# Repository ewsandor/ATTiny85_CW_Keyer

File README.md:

# ATTiny85_CW_Keyer
A full-featured CW keyer for amateur radio use. The keyer is built around a cheap and tiny ATTINY85 microcontroller. The circuit boasts 4-100 character memories, beacon mode, multiple timing options, and a CW trainer for improving your Morse code speed.

## Printed Circuit Board
This fork provides design files to build a PCB for this project.

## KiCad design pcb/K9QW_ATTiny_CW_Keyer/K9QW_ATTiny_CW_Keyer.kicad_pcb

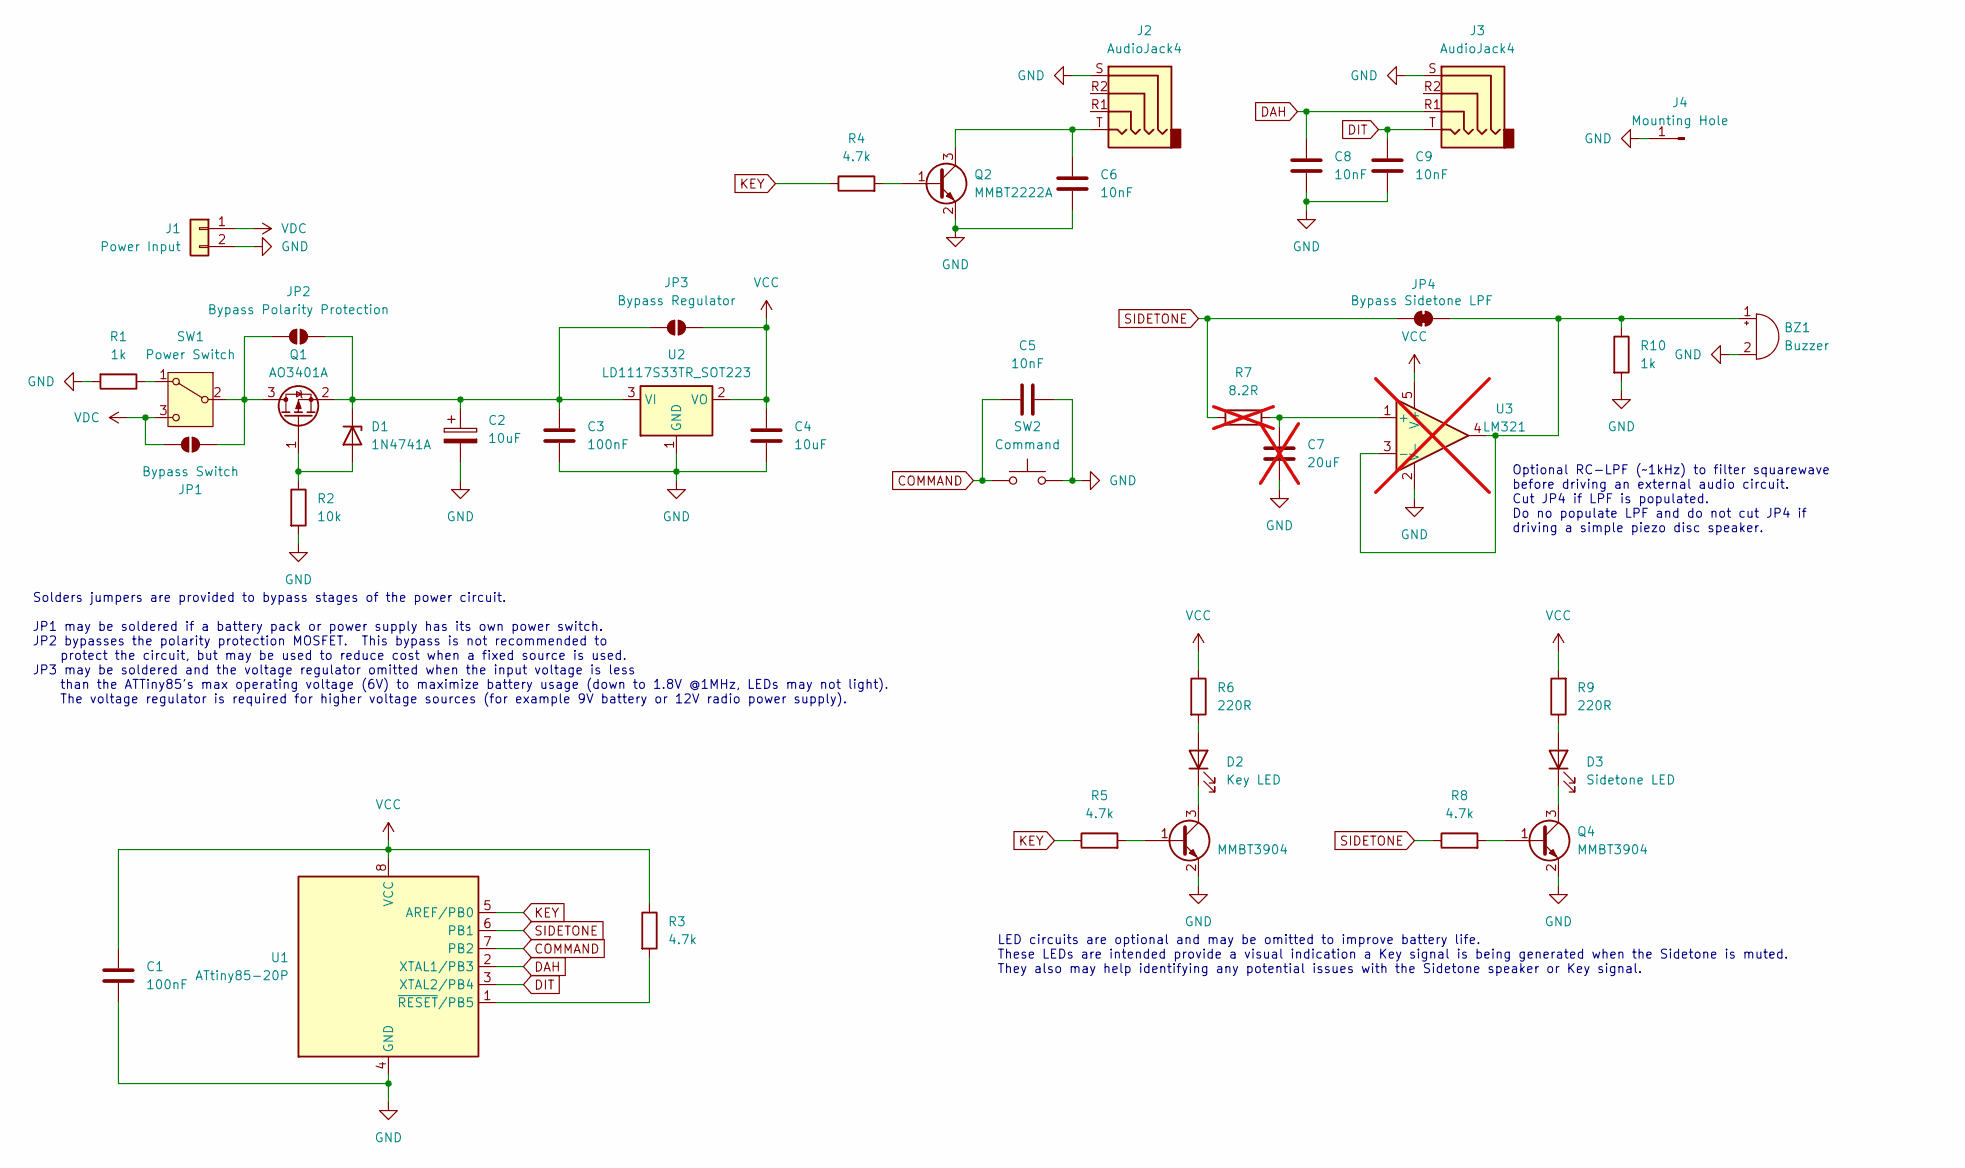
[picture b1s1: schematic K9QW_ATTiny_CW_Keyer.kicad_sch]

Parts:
BZ1: Buzzer; Buzzer_TDK_PS1240P02BT_D12.2mm_H6.5mm
C1, C3: 100nF; C_0603_1608Metric_Pad1.08x0.95mm_HandSolder
C2: 10uF; CP_Radial_D5.0mm_P2.00mm
C4: 10uF; C_0603_1608Metric_Pad1.08x0.95mm_HandSolder
C5, C6, C8, C9: 10nF; C_0603_1608Metric_Pad1.08x0.95mm_HandSolder
C7: 20uF; C_0603_1608Metric_Pad1.08x0.95mm_HandSolder; not fitted
D1: 1N4741A; D_DO-41_SOD81_P3.81mm_Vertical_KathodeUp
D2: Key LED; LED_0603_1608Metric_Pad1.05x0.95mm_HandSolder
D3: Sidetone LED; LED_0603_1608Metric_Pad1.05x0.95mm_HandSolder
J1: Power Input; JST_XH_B2B-XH-A_1x02_P2.50mm_Vertical
J2, J3: AudioJack4; Jack_3.5mm_PJ320D_Horizontal
J4: Mounting Hole; MountingHole_3.2mm_M3_Pad_TopBottom
JP1: Bypass Switch; SolderJumper-2_P1.3mm_Open_RoundedPad1.0x1.5mm
JP2: Bypass Polarity Protection; SolderJumper-2_P1.3mm_Open_RoundedPad1.0x1.5mm
JP3: Bypass Regulator; SolderJumper-2_P1.3mm_Open_RoundedPad1.0x1.5mm
JP4: Bypass Sidetone LPF; SolderJumper-2_P1.3mm_Bridged_RoundedPad1.0x1.5mm
Q1: AO3401A; SOT-23
Q2: MMBT2222A; SOT-23
Q3, Q4: MMBT3904; SOT-23
R1, R10: 1k; R_0603_1608Metric_Pad0.98x0.95mm_HandSolder
R2: 10k; R_0603_1608Metric_Pad0.98x0.95mm_HandSolder
R3, R4, R5, R8: 4.7k; R_0603_1608Metric_Pad0.98x0.95mm_HandSolder
R6, R9: 220R; R_0603_1608Metric_Pad0.98x0.95mm_HandSolder
R7: 8.2R; R_0603_1608Metric_Pad0.98x0.95mm_HandSolder; not fitted
SW1: Power Switch; JST_XH_B3B-XH-A_1x03_P2.50mm_Vertical
SW2: Command; SW_PUSH_6mm
U1: ATtiny85-20P; DIP-8_W7.62mm
U2: LD1117S33TR_SOT223; SOT-223-3_TabPin2
U3: LM321; SOT-23-5; not fitted

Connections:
COMMAND: C5.1, SW2.1, U1.7 (PB2)
DAH: C8.1, J3.R1, U1.2 (XTAL1/PB3)
DIT: C9.1, J3.T, U1.3 (XTAL2/PB4)
GND: BZ1.2 (-), C1.2, C2.2, C3.2, C4.2, C5.2, C6.2, C7.2, C8.2, C9.2, J1.2, J2.S, J3.S, J4.1, Q2.2 (E), Q3.2 (E), Q4.2 (E), R1.2, R2.2, R10.2, SW2.2, U1.4 (GND), U2.1 (GND), U3.2 (V-)
KEY: R4.1, R5.1, U1.5 (AREF/PB0)
unnamed: BZ1.1 (+), JP4.2 (B), R10.1, U3.3 (-), U3.4
unnamed: D1.2 (A), Q1.1 (G), R2.1
unnamed: C2.1, C3.1, D1.1 (K), JP2.2 (B), JP3.1 (A), Q1.2 (S), U2.3 (VI)
unnamed: D2.2 (A), R6.2
unnamed: D2.1 (K), Q3.3 (C)
unnamed: D3.2 (A), R9.1
unnamed: D3.1 (K), Q4.3 (C)
unnamed: JP1.1 (A), JP2.1 (A), Q1.3 (D), SW1.2 (B)
unnamed: Q2.1 (B), R4.2
unnamed: C6.1, J2.T, Q2.3 (C)
unnamed: Q3.1 (B), R5.2
unnamed: Q4.1 (B), R8.2
unnamed: R1.1, SW1.1 (A)
unnamed: R3.2, U1.1 (~RESET/PB5)
unnamed: C7.1, R7.1, U3.1 (+)
SIDETONE: JP4.1 (A), R7.2, R8.1, U1.6 (PB1)
VCC: C1.1, C4.1, JP3.2 (B), R3.1, R6.1, R9.2, U1.8 (VCC), U2.2 (VO), U3.5 (V+)
VDC: J1.1, JP1.2 (B), SW1.3 (C)

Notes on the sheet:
Optional RC-LPF (~1kHz) to filter squarewave before driving an external audio circuit. Cut JP4 if LPF is populated. Do no populate LPF and do not cut JP4 if driving a simple piezo disc speaker.
LED circuits are optional and may be omitted to improve battery life. These LEDs are intended provide a visual indication a Key signal is being generated when the Sidetone is muted. They also may help identifying any potential issues with the Sidetone speaker or Key signal.
Solders jumpers are provided to bypass stages of the power circuit. JP1 may be soldered if a battery pack or power supply has its own power switch. JP2 bypasses the polarity protection MOSFET. This bypass is not recommended to protect the circuit, but may be used to reduce cost when a fixed source 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

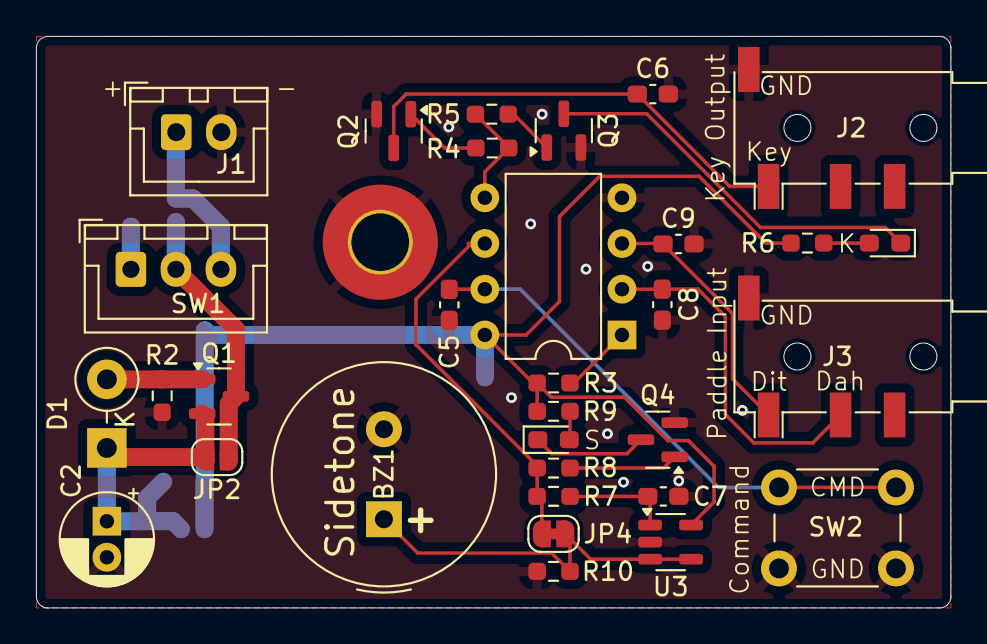
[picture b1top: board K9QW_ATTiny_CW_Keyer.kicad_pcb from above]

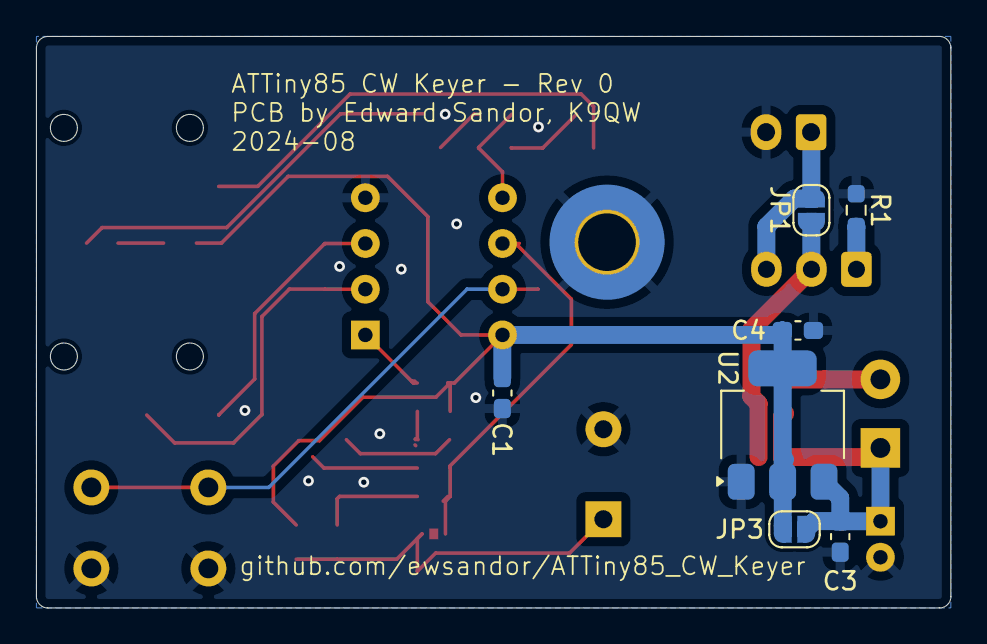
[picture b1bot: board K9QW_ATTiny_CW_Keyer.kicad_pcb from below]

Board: 2 copper layers, 50.8 x 31.8 mm, 40 parts (7 on the bottom side), 23 nets.

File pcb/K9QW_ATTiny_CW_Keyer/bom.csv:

"Reference","Value","Footprint","Qty","DNP"
"BZ1","Buzzer","Buzzer_Beeper:Buzzer_TDK_PS1240P02BT_D12.2mm_H6.5mm","1",""
"C1,C3","100nF","Capacitor_SMD:C_0603_1608Metric_Pad1.08x0.95mm_HandSolder","2",""
"C2","10uF","Capacitor_THT:CP_Radial_D5.0mm_P2.00mm","1",""
"C4","10uF","Capacitor_SMD:C_0603_1608Metric_Pad1.08x0.95mm_HandSolder","1",""
"C5,C6,C8,C9","10nF","Capacitor_SMD:C_0603_1608Metric_Pad1.08x0.95mm_HandSolder","4",""
"C7","20uF","Capacitor_SMD:C_0603_1608Metric_Pad1.08x0.95mm_HandSolder","1","DNP"
"D1","1N4741A","Diode_THT:D_DO-41_SOD81_P3.81mm_Vertical_KathodeUp","1",""
"D2","Key LED","LED_SMD:LED_0603_1608Metric_Pad1.05x0.95mm_HandSolder","1",""
"D3","Sidetone LED","LED_SMD:LED_0603_1608Metric_Pad1.05x0.95mm_HandSolder","1",""
"J1","Power Input","Connector_JST:JST_XH_B2B-XH-A_1x02_P2.50mm_Vertical","1",""
"J2,J3","AudioJack4","Connector_Audio:Jack_3.5mm_PJ320D_Horizontal","2",""
"J4","Mounting Hole","MountingHole:MountingHole_3.2mm_M3_Pad_TopBottom","1",""
"Q1","AO3401A","Package_TO_SOT_SMD:SOT-23","1",""
"Q2","MMBT2222A","Package_TO_SOT_SMD:SOT-23","1",""
"Q3,Q4","MMBT3904","Package_TO_SOT_SMD:SOT-23","2",""
"R1","1k","Resistor_SMD:R_0603_1608Metric_Pad0.98x0.95mm_HandSolder","1",""
"R2","10k","Resistor_SMD:R_0603_1608Metric_Pad0.98x0.95mm_HandSolder","1",""
"R3,R4,R5,R8","4.7k","Resistor_SMD:R_0603_1608Metric_Pad0.98x0.95mm_HandSolder","4",""
"R6,R9","220R","Resistor_SMD:R_0603_1608Metric_Pad0.98x0.95mm_HandSolder","2",""
"R7","8.2R","Resistor_SMD:R_0603_1608Metric_Pad0.98x0.95mm_HandSolder","1","DNP"
"SW1","Power Switch","Connector_JST:JST_XH_B3B-XH-A_1x03_P2.50mm_Vertical","1",""
"SW2","Command","Button_Switch_THT:SW_PUSH_6mm","1",""
"U1","ATtiny85-20P","Package_DIP:DIP-8_W7.62mm","1",""
"U2","LD1117S33TR_SOT223","Package_TO_SOT_SMD:SOT-223-3_TabPin2","1",""
"U3","LM321","Package_TO_SOT_SMD:SOT-23-5","1","DNP"

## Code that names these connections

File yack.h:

/* ********************************************************************
 Program	: yack.h
 Author		: Jan Lategahn DK3LJ modified by Jack Welch AI4SV, Don Froula WD9DMP
 Purpose	: definition of keyer hardware
 Created	: 15.10.2010
 Update		: 23.12.2016
 Version	: 0.86
 
 Changelog
 ---------
 Version		Date		Change
 ----------------------------------------------------------------------
0.86          23.12.2016    Changed sidetone back to 800 Hz and mode default to iambicB  
 
 Todo
 ----
 
 
 *********************************************************************/

// User configurable settings

// The following settings define the hardware connections to the keyer chip

// Definition of where the keyer itself is connected 
#define		KEYDDR			DDRB
#define		KEYPORT			PORTB
#define		KEYINP			PINB
#define		DITPIN			4
#define		DAHPIN			3

// Definition of where the transceiver keyer line is connected
#define		OUTDDR			DDRB
#define		OUTPORT			PORTB
#define		OUTPIN			0

// Definition of where the sidetone output is connected (beware,
// this is chip dependent and can not just be changed at will)
#define		STDDR			DDRB
#define		STPORT			PORTB
#define		STPIN			1

// Definition of where the control button is connected
#define		BTNDDR			DDRB
#define		BTNPORT			PORTB
#define		BTNINP			PINB
#define		BTNPIN			2


// The following defines the meaning of status bits in the yackflags and volflags 
// global variables

// Definition of the yackflags variable. These settings get stored in EEPROM when changed.
#define		NOTUSED1		0b00000001  // Available
#define     CONFLOCK		0b00000010  // Configuration locked down
#define		MODE			0b00001100  // 2 bits to define keyer mode (see next section)
#define		SIDETONE		0b00010000  // Set if the chip must produce a sidetone
#define		TXKEY			0b00100000  // Set if the chip keys the transmitter
#define		TXINV			0b01000000  // Set if TX key line is active low
#define		PDLSWAP			0b10000000  // Set if DIT and DAH are swapped

#define		IAMBICA			0b00000000  // IAMBIC A mode
#define		IAMBICB			0b00000100  // IAMBIC B mode (default)
#define		ULTIMATIC		0b00001000  // Ultimatic Mode
#define		DAHPRIO			0b00001100  // Always give DAH priority

#define		FLAGDEFAULT		IAMBICB | TXKEY | SIDETONE

// Definition of volflags variable. These flags do not get stored in EEPROM.
#define		DITLATCH		0b00000001  // Set if DIT contact was closed
#define     DAHLATCH		0b00000010  // Set if DAH contact was closed
#define     SQUEEZED        0b00000011  // DIT and DAH = squeezed
#define		DIRTYFLAG		0b00000100  // Set if cfg data was changed and needs storing
#define     CKLATCH         0b00001000  // Set if the command key was pressed at some point
#define		VSCOPY          0b00110000  // Copies of Sidetone and TX flags from yackflags


// The following defines timing constants. In the default version the keyer is set to operate in
// 10ms heartbeat intervals. If a higher resolution is required, this can be changed to a faster
// beat

// YACK heartbeat frequency (in ms)
#define		YACKBEAT		5
#define		YACKSECS(n)		(n*(1000/YACKBEAT)) // Beats in n seconds (off by 2x for 5ms heartbeat)
#define		YACKMS(n)		(n/YACKBEAT) // Beats in n milliseconds

// Power save mode
#define     POWERSAVE       // Comment this line if no power save mode required
#define     PSTIME          20 // 20 seconds until automatic powerdown
#define     PWRWAKE         ((1<<PCINT3) | (1<<PCINT4) | (1<<PCINT2)) // Dit, Dah or Command wakes us up..

// These values limit the speed that the keyer can be set to
#define		MAXWPM			50  
#define		MINWPM			5
#define		DEFWPM			15

// Farnsworth parameters
#define     FARNSWORTH      1
#define     WPMSPEED        0
#define     MAXFARN         255

#define		WPMCALC(n)		((1200/YACKBEAT)/n) // Calculates number of beats in a dot 

#define		DITLEN			1	// Length of a dot
#define		DAHLEN			3	// Length of a dash
#define		IEGLEN			1	// Length of inter-element gap
#define		ICGLEN			3	// Length of inter-character gap
#define		IWGLEN			7	// Length of inter-word gap

// Duration of various internal timings in seconds
#define		TUNEDURATION	20  // Duration of tuning keydown (in seconds)
#define     DEFTIMEOUT      5   // Default timeout 5 seconds
#define     MACTIMEOUT      15  // Timeout after playing back a macro

// The following defines various parameters in relation to the pitch of the sidetone

// CTC mode prescaler.. If changing this, ensure that ctc config
// is adapted accordingly
#define		PRESCALE		8
#define		CTCVAL(n)		((F_CPU/n/2/PRESCALE)-1) // Defines how to compute CTC setting for
                                                     // a given frequency

// Default sidetone frequency
#define		DEFFREQ			800     // Default sidetone frequency
#define		MAXFREQ			1500    // Maximum frequency
#define		MINFREQ			400     // Minimum frequency

#define		MAXCTC			CTCVAL(MAXFREQ) // CTC values for the above three values
#define		MINCTC			CTCVAL(MINFREQ) 
#define		DEFCTC			CTCVAL(DEFFREQ)

// The following are various definitions in use throughout the program
#define		RBSIZE			100     // Size of each of the four EEPROM buffers

#define		MAGPAT			0xA5    // If this number is found in EEPROM, content assumed valid

#define		DIT				1
#define		DAH             2

#define		UP				1
#define		DOWN			2

#define		ON				1
#define		OFF				0

#define		RECORD			1
#define		PLAY			2

#define		READ			1
#define		WRITE			2

#define		TRUE            1
#define		FALSE           0


// Generic functionality
#define 	SETBIT(ADDRESS,BIT)     (ADDRESS |= (1<<BIT))
#define 	CLEARBIT(ADDRESS,BIT)   (ADDRESS &= ~(1<<BIT))

typedef		uint8_t         byte;
typedef		uint16_t        word;


// Forward declarations of public functions
void        yackinit (void);
void        yackchar(char c);
void        yackstring(const char *p);
char        yackiambic(byte ctrl);
void        yackpitch (uint8_t dir);
void        yacktune (void);
void        yackmode (uint8_t mode);
void        yackinhibit (uint8_t mode);
void        yackerror (void);
void        yacktoggle(byte flag);
byte        yackflag(byte flag);
void        yackbeat(void);
void        yackmessage(byte function, byte msgnr);
void        yacksave (void);
byte        yackctrlkey(byte mode);
void        yackreset (void);
word        yackuser (byte func, byte nr, word content);
void        yacknumber(word n);
word        yackwpm(void);
void        yackplay(byte i);
void        yackdelay(byte n);
void        yackfarns(void);
void        yackspeed (byte dir, byte mode);

#ifdef POWERSAVE
void        yackpower(byte n);
#endif

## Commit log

2024-08-11 PCB Draft
2024-08-12 Fixing LED and adding Sidetone Connector
2024-08-12 Minor
2024-08-12 Rough PCB Layout
2024-08-12 Rough routing
2024-08-12 Layout cleanup
2024-08-12 Refining layout
2024-08-12 Refining routing
2024-08-12 Adding git ignore for local KiCAD Files
2024-08-12 Stripping panel mount headers
2024-08-13 Removed panel headers, added reverse polarity protection, rough layout
2024-08-13 Routing signals
2024-08-13 Minor adjustments
2024-08-13 Filter cap for command button
2024-08-13 Optional LPF and reordering input/output connectors
2024-08-13 Readme note, updated schematic, generated Gerbers
2024-08-13 Rounding edges
2024-08-13 Adding power supply filter cap and preparing buzzer
2024-08-14 Laying out buzzer and moving power regulator to back of board
2024-08-14 Regenerating supporting files
2024-08-14 Minor adjustment
2024-08-14 Buffer for LPF
2024-08-14 Update release files
2024-08-14 Adding resistor for 'charging and discharging to a piezoelectric element' as per buzzer datasheet.
2024-08-14 Regenerating release files
2024-08-14 Disable failing debug extcoff in makefile. Specify MCU in ELF size command
2024-08-17 Update programming commmand to use Sparkfun's usbtiny programmer
2024-08-17 Reduce sleep delay
2024-08-18 Even shorter power save interval
2024-08-18 Sleep delay at least as long as each timeout
2024-08-19 Default sidetone of 600Hz
2024-08-19 Recommend omitting sidetone LED by default
2024-08-19 Update exported schematic and bom
2024-08-19 .gitignore build files
2024-08-29 Matching dit/dah pins to PCB, set 800hz sidetone to match Kenwood TS-690s
2024-09-19 Simple enclosure to contain PCB and 2032 Battery
